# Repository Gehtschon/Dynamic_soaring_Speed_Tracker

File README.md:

# Dynamic_soaring_Speed_Tracker

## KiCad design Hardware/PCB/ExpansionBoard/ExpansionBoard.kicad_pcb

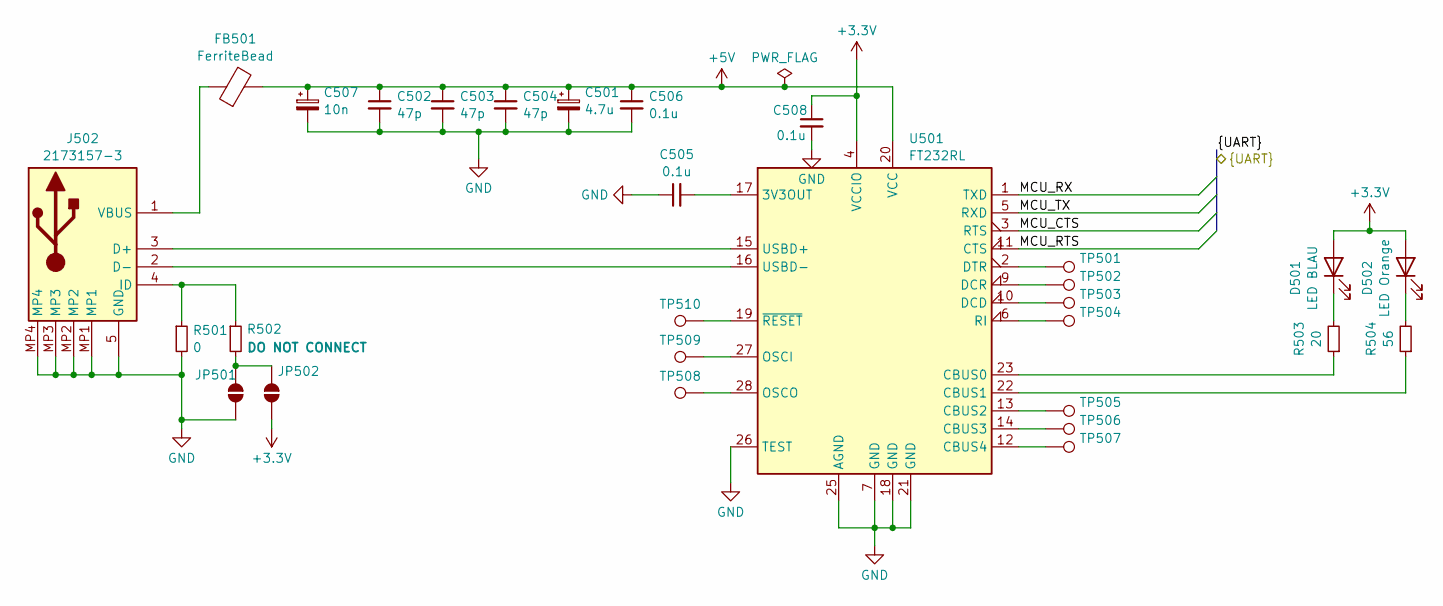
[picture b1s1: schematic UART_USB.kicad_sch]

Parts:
C501: 4.7u; C_0805_2012Metric_Pad1.18x1.45mm_HandSolder
C502, C503, C504: 47p; C_0805_2012Metric_Pad1.18x1.45mm_HandSolder
C505, C506, C508: 0.1u; C_0805_2012Metric_Pad1.18x1.45mm_HandSolder
C507: 10n; C_0805_2012Metric_Pad1.18x1.45mm_HandSolder
D501: LED BLAU; LEDM2012X100N
D502: LED Orange; R_0805_2012Metric
FB501: FerriteBead; C_0805_2012Metric_Pad1.18x1.45mm_HandSolder
J502: 2173157-3; 21731573; Mouser Part Number 571-2173157-3
JP501, JP502: SolderJumper_2_Open; SolderJumper-2_P1.3mm_Open_RoundedPad1.0x1.5mm
R501: 0; R_0805_2012Metric_Pad1.20x1.40mm_HandSolder
R502: DO NOT CONNECT; R_0805_2012Metric_Pad1.20x1.40mm_HandSolder
R503: 20; R_0805_2012Metric_Pad1.20x1.40mm_HandSolder
R504: 56; R_0805_2012Metric_Pad1.20x1.40mm_HandSolder
TP501, TP502, TP503, TP504, TP505, TP506, TP507, TP508, TP509, TP510: TestPoint; TestPoint_Pad_D1.5mm
U501: FT232RL; SSOP-28_5.3x10.2mm_P0.65mm

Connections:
+3.3V: C508.1, D501.2 (A), D502.2 (A), JP502.1 (A), U501.4 (VCCIO); also elsewhere on the board
+5V: C501.1, C502.1, C503.1, C504.1, C506.1, C507.1, FB501.2, U501.20 (VCC); also elsewhere on the board
/MCU Sheet/MCU_CTS: U501.3 (RTS); also elsewhere on the board
/MCU Sheet/MCU_RTS: U501.11 (CTS); also elsewhere on the board
/MCU Sheet/MCU_RX: U501.1 (TXD); also elsewhere on the board
/MCU Sheet/MCU_TX: U501.5 (RXD); also elsewhere on the board
GND: C501.2, C502.2, C503.2, C504.2, C505.1, C506.2, C507.2, C508.2, J502.5 (GND), J502.MP1, J502.MP2, J502.MP3, J502.MP4, JP501.1 (A), R501.2, U501.7 (GND), U501.18 (GND), U501.21 (GND), U501.25 (AGND), U501.26 (TEST); also elsewhere on the board
unnamed: D501.1 (K), R503.2
unnamed: D502.1 (K), R504.2
unnamed: J502.3 (D+), U501.15 (USBD+)
unnamed: J502.2 (D-), U501.16 (USBD-)
unnamed: J502.4 (ID), R501.1, R502.1
unnamed: FB501.1, J502.1 (VBUS)
unnamed: JP501.2 (B), JP502.2 (B), R502.2
unnamed: C505.2, U501.17 (3V3OUT)
unnamed: R503.1, U501.23 (CBUS0)
unnamed: R504.1, U501.22 (CBUS1)
unnamed: TP505.1, U501.13 (CBUS2)
unnamed: TP506.1, U501.14 (CBUS3)
unnamed: TP507.1, U501.12 (CBUS4)
unnamed: TP503.1, U501.10 (DCD)
unnamed: TP502.1, U501.9 (DCR)
unnamed: TP501.1, U501.2 (DTR)
unnamed: TP509.1, U501.27 (OSCI)
unnamed: TP508.1, U501.28 (OSCO)
unnamed: TP504.1, U501.6 (RI)
unnamed: TP510.1, U501.19 (~RESET)

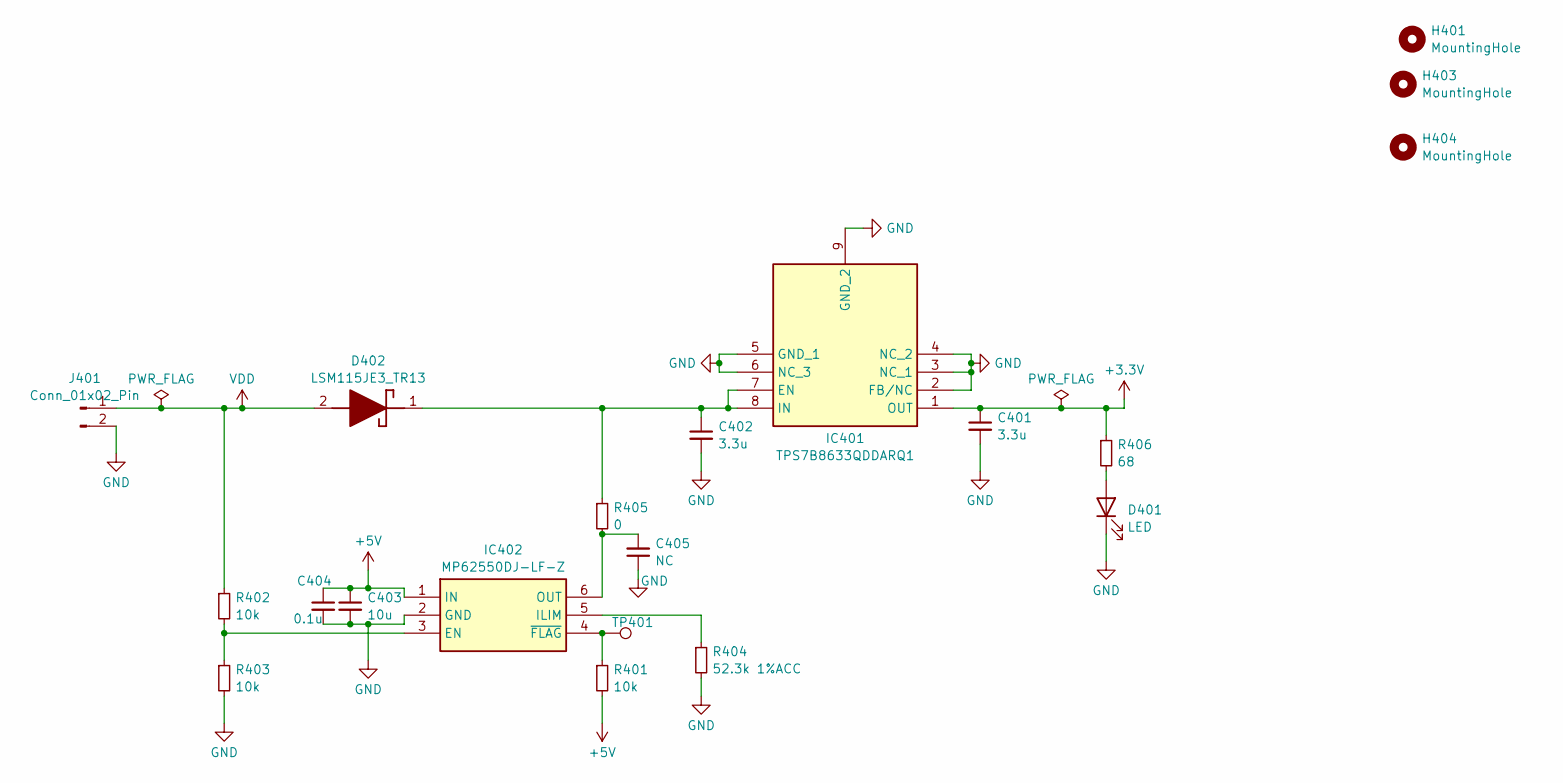
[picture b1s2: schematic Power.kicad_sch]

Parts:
C401, C402: 3.3u; C_0805_2012Metric_Pad1.18x1.45mm_HandSolder
C403: 10u; C_0805_2012Metric_Pad1.18x1.45mm_HandSolder
C404: 0.1u; C_0805_2012Metric_Pad1.18x1.45mm_HandSolder
C405: NC; C_0805_2012Metric_Pad1.18x1.45mm_HandSolder
D401: LED; LEDC2012X80N
D402: LSM115JE3_TR13; DIOM5436X330N; Mouser Part Number 494-LSM115JE3/TR13
H401, H403, H404: MountingHole; MountingHole_2.2mm_M2
IC401: TPS7B8633QDDARQ1; SOIC127P600X170-9N; Mouser Part Number 595-TPS7B8633QDDARQ1
IC402: MP62550DJ-LF-Z; SOT95P280X100-6N; Mouser Part Number 946-MP62550DJLFZ
J401: Conn_01x02_Pin; PinHeader_1x02_P2.54mm_Vertical
R401, R402, R403: 10k; R_0805_2012Metric_Pad1.20x1.40mm_HandSolder
R404: 52.3k 1%ACC; R_0805_2012Metric_Pad1.20x1.40mm_HandSolder
R405: 0; R_0805_2012Metric_Pad1.20x1.40mm_HandSolder
R406: 68; R_0805_2012Metric_Pad1.20x1.40mm_HandSolder
TP401: TestPoint; TestPoint_Pad_D1.5mm

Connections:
+3.3V: C401.1, IC401.1 (OUT), R406.1; also elsewhere on the board
+5V: C403.1, C404.1, IC402.1 (IN), R401.2; also elsewhere on the board
GND: C401.2, C402.2, C403.2, C404.2, C405.1, D401.1 (K), IC401.2 (FB/NC), IC401.3 (NC_1), IC401.4 (NC_2), IC401.5 (GND_1), IC401.6 (NC_3), IC401.9 (GND_2), IC402.2 (GND), J401.2, R403.2, R404.2; also elsewhere on the board
unnamed: D401.2 (A), R406.2
unnamed: C402.1, D402.1 (K), IC401.7 (EN), IC401.8 (IN), R405.1
unnamed: IC402.3 (EN), R402.2, R403.1
unnamed: IC402.5 (ILIM), R404.1
unnamed: C405.2, IC402.6 (OUT), R405.2
unnamed: IC402.4 (~FLAG), R401.1, TP401.1
VDD: D402.2 (A), J401.1, R402.1

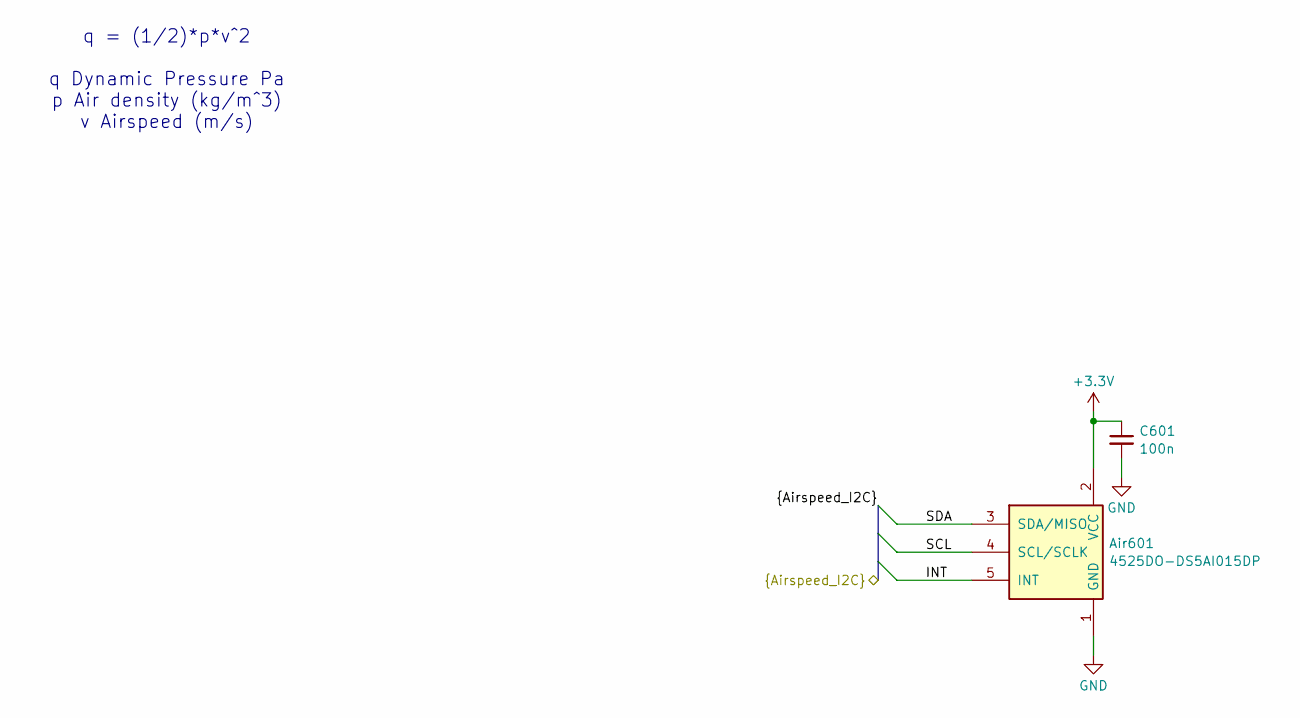
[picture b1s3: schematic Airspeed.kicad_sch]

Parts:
Air601: 4525DO-DS5AI015DP
C601: 100n; C_0805_2012Metric_Pad1.18x1.45mm_HandSolder

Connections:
+3.3V: Air601.2 (VCC), C601.1; also elsewhere on the board
/Airspeed Sheet/INT: Air601.5 (INT); also elsewhere on the board
/Airspeed Sheet/SCL: Air601.4 (SCL/SCLK); also elsewhere on the board
/Airspeed Sheet/SDA: Air601.3 (SDA/MISO); also elsewhere on the board
GND: Air601.1 (GND), C601.2; also elsewhere on the board

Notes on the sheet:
q = (1/2)*p*v^2 q Dynamic Pressure Pa p Air density (kg/m^3) v Airspeed (m/s)

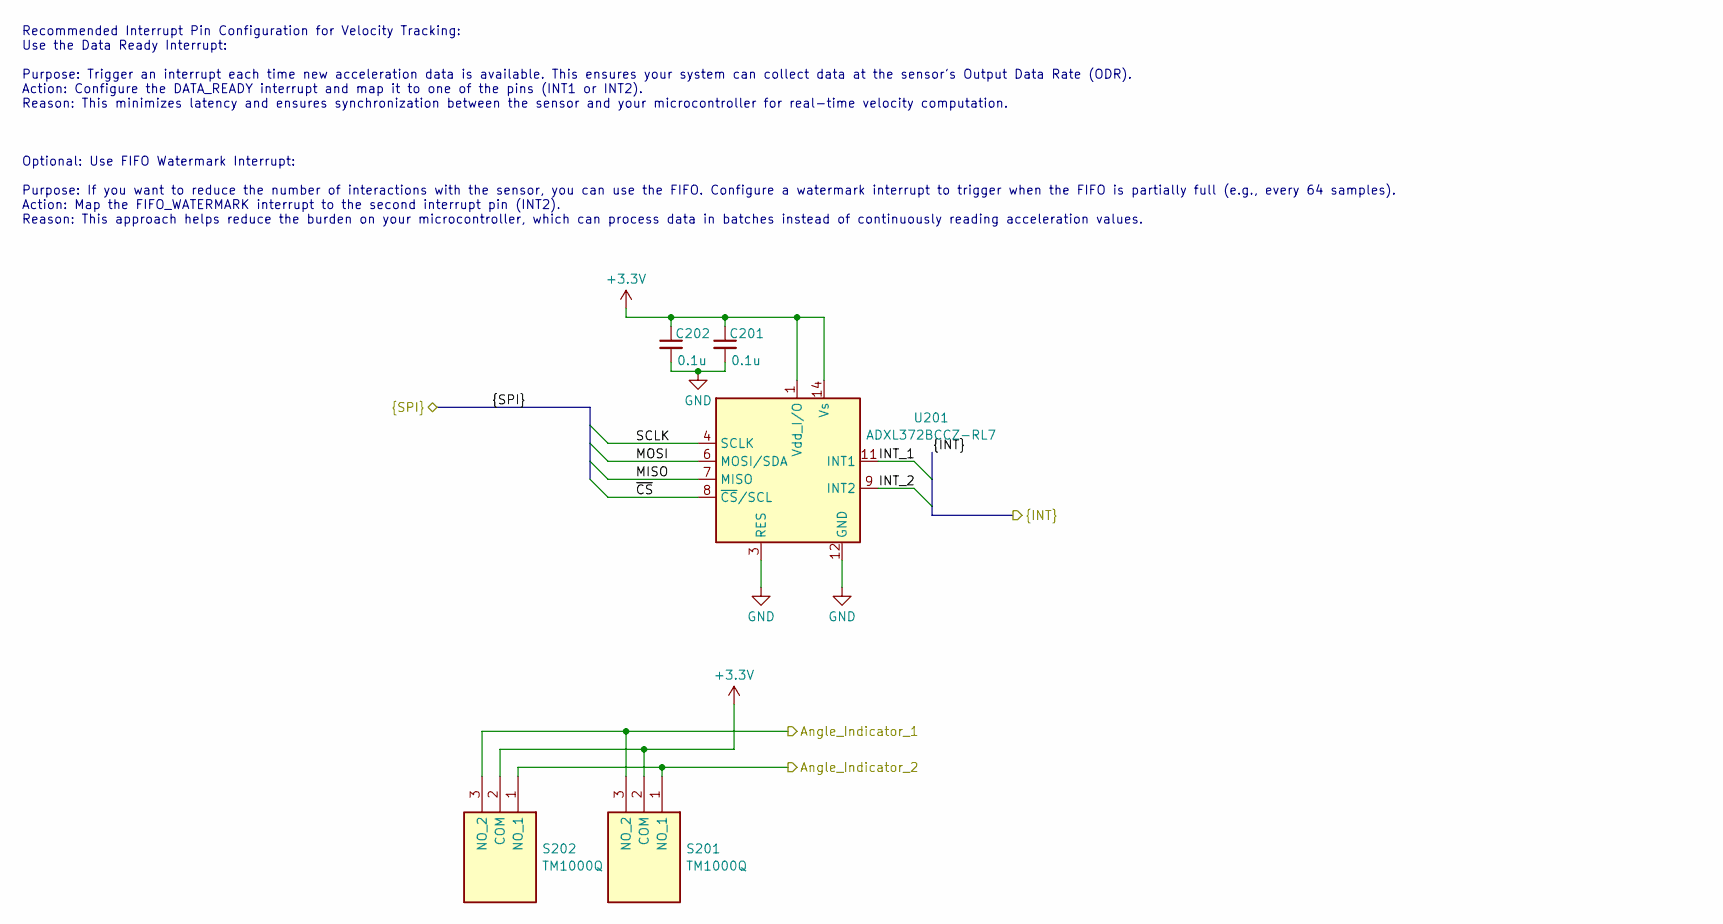
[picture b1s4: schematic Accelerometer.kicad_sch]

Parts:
C201, C202: 0.1u; C_0805_2012Metric_Pad1.18x1.45mm_HandSolder
S201, S202: TM1000Q; Mouser Part Number 612-TM1000Q
U201: ADXL372BCCZ-RL7

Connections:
+3.3V: C201.1, C202.1, S201.2 (COM), S202.2 (COM), U201.1 (Vdd_I/O), U201.14 (Vs); also elsewhere on the board
/Accelerometer.Sheet/Angle_Indicator_1: S201.3 (NO_2), S202.3 (NO_2); also elsewhere on the board
/Accelerometer.Sheet/Angle_Indicator_2: S201.1 (NO_1), S202.1 (NO_1); also elsewhere on the board
/Accelerometer.Sheet/INT_1: U201.11 (INT1); also elsewhere on the board
/Accelerometer.Sheet/INT_2: U201.9 (INT2); also elsewhere on the board
/Accelerometer.Sheet/MISO: U201.7 (MISO); also elsewhere on the board
/Accelerometer.Sheet/MOSI: U201.6 (MOSI/SDA); also elsewhere on the board
/Accelerometer.Sheet/SCLK: U201.4 (SCLK); also elsewhere on the board
/Accelerometer.Sheet/~CS: U201.8 (~CS/SCL); also elsewhere on the board
GND: C201.2, C202.2, U201.3 (RES), U201.5 (RES), U201.10 (RES), U201.12 (GND), U201.13 (GND), U201.16 (GND); also elsewhere on the board

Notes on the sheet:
Recommended Interrupt Pin Configuration for Velocity Tracking: Use the Data Ready Interrupt: Purpose: Trigger an interrupt each time new acceleration data is available. This ensures your system can collect data at the sensor's Output Data Rate (ODR). Action: Configure the DATA_READY interrupt and m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

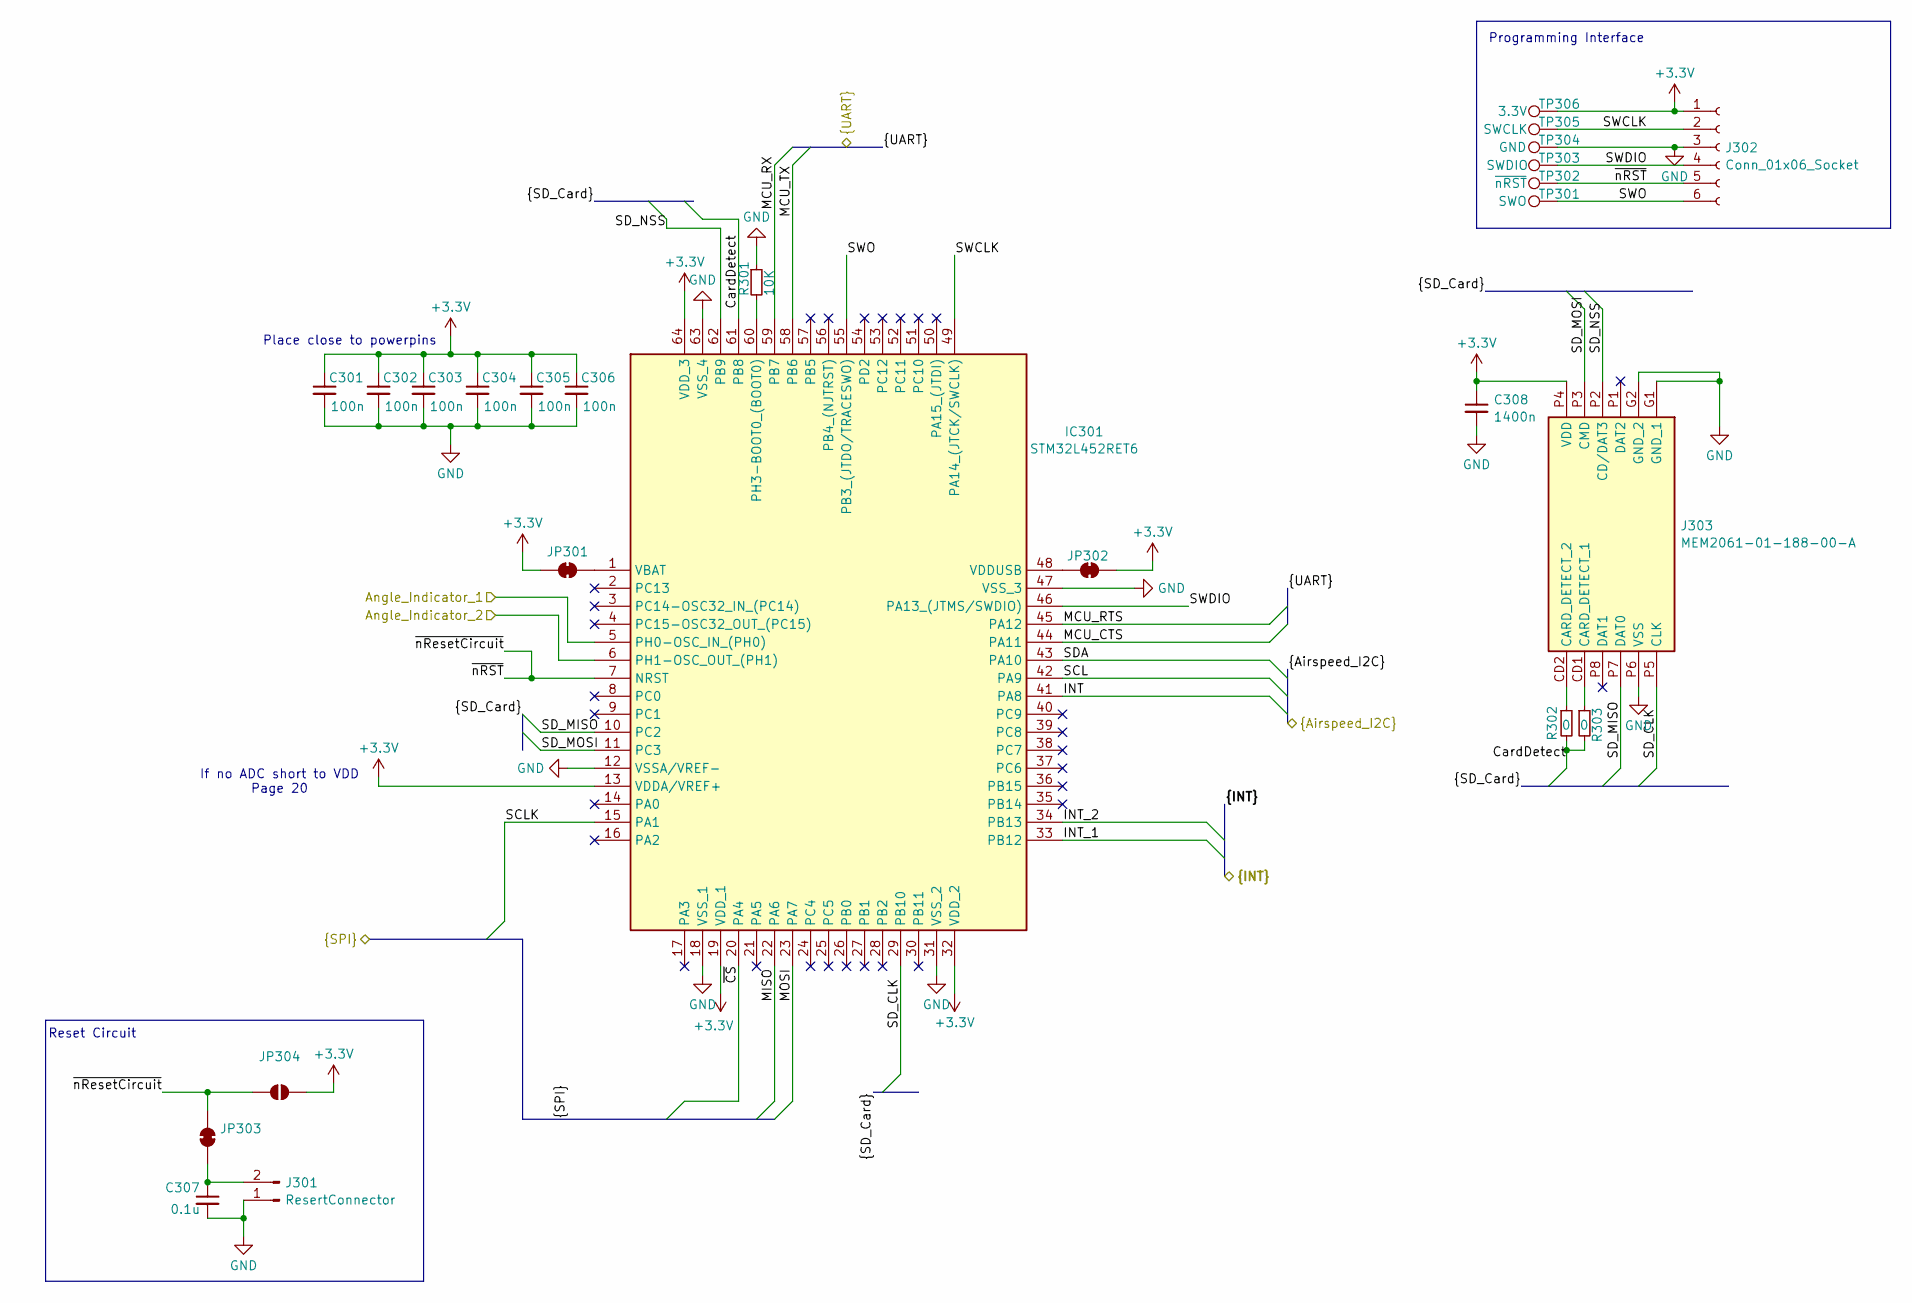
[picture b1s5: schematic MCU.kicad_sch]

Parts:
C301, C302, C303, C304, C305, C306: 100n; C_0805_2012Metric_Pad1.18x1.45mm_HandSolder
C307: 0.1u; C_0805_2012Metric_Pad1.18x1.45mm_HandSolder
C308: 1400n; C_0805_2012Metric_Pad1.18x1.45mm_HandSolder
IC301: STM32L452RET6; QFP50P1200X1200X160-64N; Mouser Part Number 511-STM32L452RET6
J301: ResertConnector; PinHeader_1x02_P2.54mm_Vertical
J302: Conn_01x06_Socket; Tag-Connect_TC2030-IDC-FP_2x03_P1.27mm_Vertical
J303: MEM2061-01-188-00-A; MEM20610118800A; Mouser Part Number 640-MEM20610118800A
JP301, JP302, JP303: SolderJumper_2_Bridged; SolderJumper-2_P1.3mm_Bridged_RoundedPad1.0x1.5mm
JP304: SolderJumper_2_Open; SolderJumper-2_P1.3mm_Open_RoundedPad1.0x1.5mm
R301: 10K; R_0805_2012Metric_Pad1.20x1.40mm_HandSolder
R302, R303: 0; R_0805_2012Metric_Pad1.20x1.40mm_HandSolder
TP301: SWO; TestPoint_Pad_D1.5mm
TP302: ~{nRST}; TestPoint_Pad_D1.5mm
TP303: SWDIO; TestPoint_Pad_D1.5mm
TP304: GND; TestPoint_Pad_D1.5mm
TP305: SWCLK; TestPoint_Pad_D1.5mm
TP306: 3.3V; TestPoint_Pad_D1.5mm

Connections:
+3.3V: C301.1, C302.1, C303.1, C304.1, C305.1, C306.1, C308.1, IC301.13 (VDDA/VREF+), IC301.19 (VDD_1), IC301.32 (VDD_2), IC301.64 (VDD_3), J302.1, J303.P4 (VDD), JP301.1 (A), JP302.1 (A), JP304.2 (B), TP306.1; also elsewhere on the board
/Accelerometer.Sheet/Angle_Indicator_1: IC301.5 (PH0-OSC_IN_(PH0)); also elsewhere on the board
/Accelerometer.Sheet/Angle_Indicator_2: IC301.6 (PH1-OSC_OUT_(PH1)); also elsewhere on the board
/Accelerometer.Sheet/INT_1: IC301.33 (PB12); also elsewhere on the board
/Accelerometer.Sheet/INT_2: IC301.34 (PB13); also elsewhere on the board
/Accelerometer.Sheet/MISO: IC301.22 (PA6); also elsewhere on the board
/Accelerometer.Sheet/MOSI: IC301.23 (PA7); also elsewhere on the board
/Accelerometer.Sheet/SCLK: IC301.15 (PA1); also elsewhere on the board
/Accelerometer.Sheet/~CS: IC301.20 (PA4); also elsewhere on the board
/Airspeed Sheet/INT: IC301.41 (PA8); also elsewhere on the board
/Airspeed Sheet/SCL: IC301.42 (PA9); also elsewhere on the board
/Airspeed Sheet/SDA: IC301.43 (PA10); also elsewhere on the board
/MCU Sheet/CardDetect: IC301.61 (PB8), R302.2, R303.2
/MCU Sheet/MCU_CTS: IC301.44 (PA11); also elsewhere on the board
/MCU Sheet/MCU_RTS: IC301.45 (PA12); also elsewhere on the board
/MCU Sheet/MCU_RX: IC301.59 (PB7); also elsewhere on the board
/MCU Sheet/MCU_TX: IC301.58 (PB6); also elsewhere on the board
/MCU Sheet/SD_CLK: IC301.29 (PB10), J303.P5 (CLK)
/MCU Sheet/SD_MISO: IC301.10 (PC2), J303.P7 (DAT0)
/MCU Sheet/SD_MOSI: IC301.11 (PC3), J303.P3 (CMD)
/MCU Sheet/SD_NSS: IC301.62 (PB9), J303.P2 (CD/DAT3)
/MCU Sheet/SWCLK: IC301.49 (PA14_(JTCK/SWCLK)), J302.2, TP305.1
/MCU Sheet/SWDIO: IC301.46 (PA13_(JTMS/SWDIO)), J302.4, TP303.1
/MCU Sheet/SWO: IC301.55 (PB3_(JTDO/TRACESWO)), J302.6, TP301.1
/MCU Sheet/~nRST: IC301.7 (NRST), J302.5, JP303.2 (B), JP304.1 (A), TP302.1
GND: C301.2, C302.2, C303.2, C304.2, C305.2, C306.2, C307.2, C308.2, IC301.12 (VSSA/VREF-), IC301.18 (VSS_1), IC301.31 (VSS_2), IC301.47 (VSS_3), IC301.63 (VSS_4), J301.1, J302.3, J303.G1 (GND_1), J303.G2 (GND_2), J303.P6 (VSS), R301.1, TP304.1; also elsewhere on the board
unnamed: IC301.60 (PH3-BOOT0_(BOOT0)), R301.2
unnamed: IC301.1 (VBAT), JP301.2 (B)
unnamed: IC301.48 (VDDUSB), JP302.2 (B)
unnamed: C307.1, J301.2, JP303.1 (A)
unnamed: J303.CD1 (CARD_DETECT_1), R303.1
unnamed: J303.CD2 (CARD_DETECT_2), R302.1

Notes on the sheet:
Programming Interface
If no ADC short to VDD Page 20
Reset Circuit
Place close to powerpins

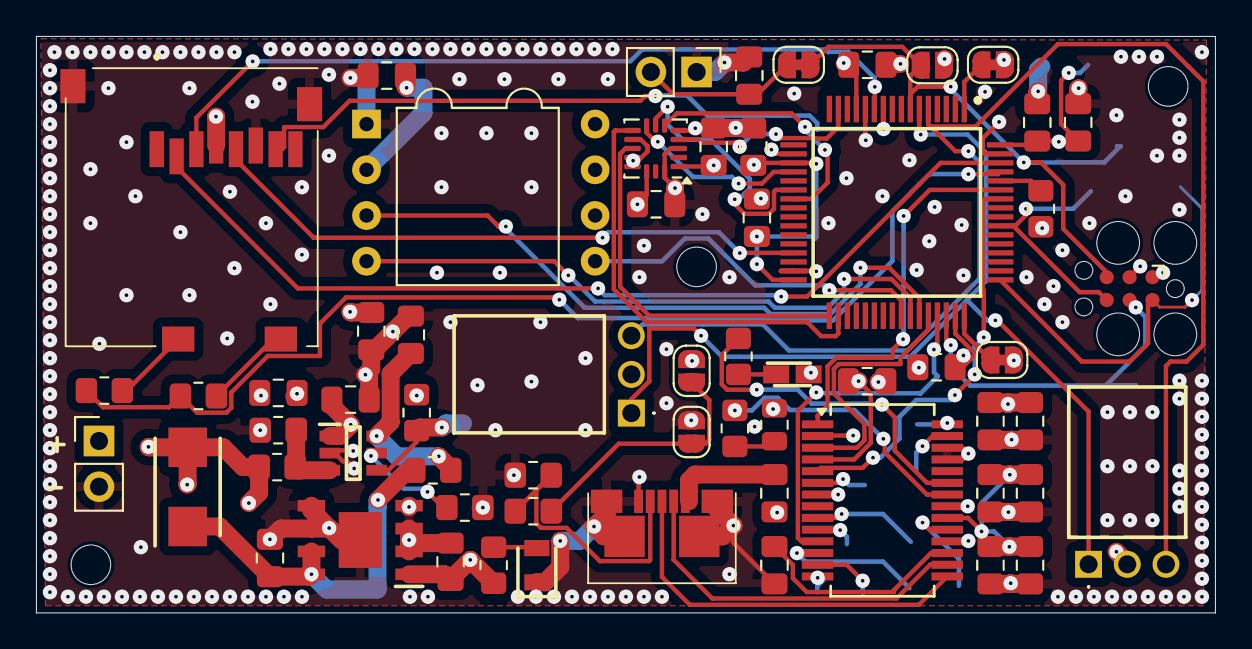
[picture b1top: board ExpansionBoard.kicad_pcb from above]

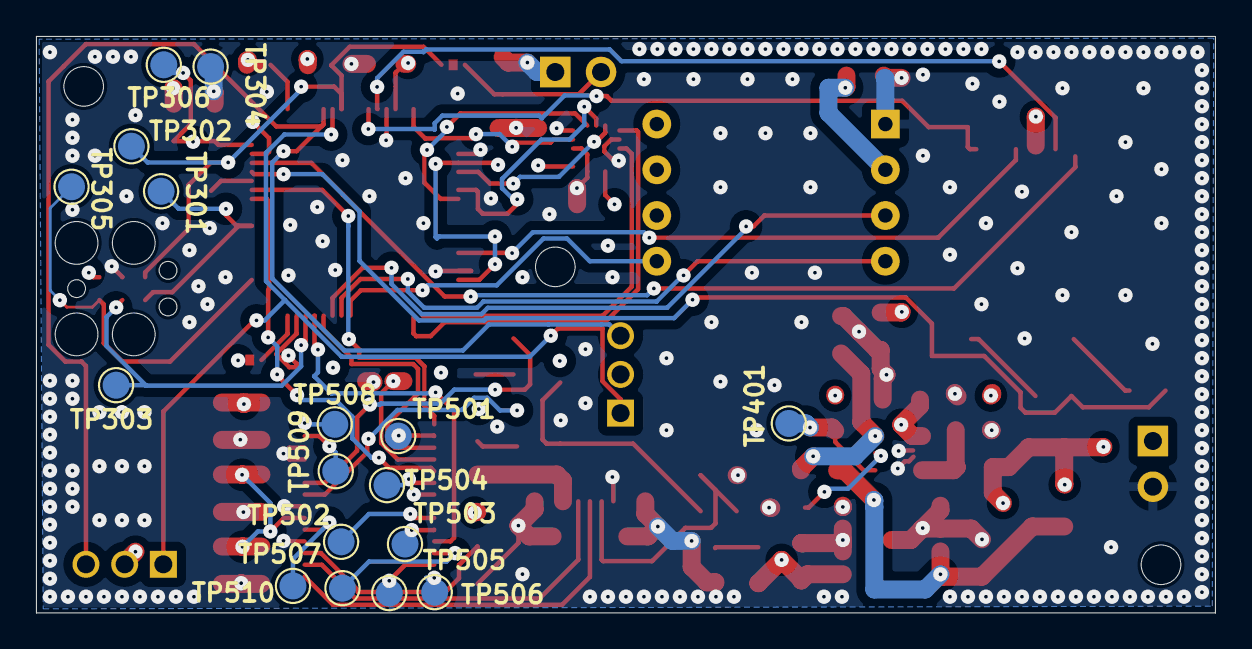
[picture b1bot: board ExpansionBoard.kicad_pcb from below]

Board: 4 copper layers, 65.5 x 32.0 mm, 81 parts (17 on the bottom side), 60 nets.

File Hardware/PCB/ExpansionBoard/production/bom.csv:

Designator,Footprint,Quantity,Value,LCSC Part #
AIR601,4525DO-DS5AI015DP,1,4525DO-DS5AI015DP,
"C201, C202, C307, C404, C505, C506, C508",0805,7,0.1u,
"C301, C302, C303, C304, C305, C306, C601",0805,7,100n,
C308,0805,1,1400n,
"C401, C402",0805,2,3.3u,
C403,0805,1,10u,
C405,0805,1,NC,
C501,0805,1,4.7u,
"C502, C503, C504",0805,3,47p,
C507,0805,1,10n,
D401,LEDC2012X80N,1,LED,
D402,DIOM5436X330N,1,LSM115JE3_TR13,
D501,LEDM2012X100N,1,LED BLAU,
D502,0805,1,LED Orange,
FB501,0805,1,FerriteBead,
IC301,QFP50P1200X1200X160-64N,1,STM32L452RET6,
IC401,SOIC127P600X170-9N,1,TPS7B8633QDDARQ1,
IC402,SOT95P280X100-6N,1,MP62550DJ-LF-Z,
J301,PinHeader_1x02_P2.54mm_Vertical,1,ResertConnector,
J302,Tag-Connect_TC2030-IDC-FP_2x03_P1.27mm_Vertical,1,Conn_01x06_Socket,
J303,MEM20610118800A,1,MEM2061-01-188-00-A,
J401,PinHeader_1x02_P2.54mm_Vertical,1,Conn_01x02_Pin,
J502,21731573,1,2173157-3,
"R301, R401, R402, R403",0805,4,10K,
"R302, R303, R405, R501",0805,4,0,
R404,0805,1,52.3k 1%ACC,
R406,0805,1,68,
R502,0805,1,DO NOT CONNECT,
R503,0805,1,20,
R504,0805,1,56,
"S201, S202",TM1000Q,2,TM1000Q,
TP301,TestPoint_Pad_D1.5mm,1,SWO,
TP302,TestPoint_Pad_D1.5mm,1,~{nRST},
TP303,TestPoint_Pad_D1.5mm,1,SWDIO,
TP304,TestPoint_Pad_D1.5mm,1,GND,
TP305,TestPoint_Pad_D1.5mm,1,SWCLK,
TP306,TestPoint_Pad_D1.5mm,1,3.3V,
"TP401, TP501, TP502, TP503, TP504, TP505, TP506, TP507, TP508, TP509, TP510",TestPoint_Pad_D1.5mm,11,TestPoint,
U201,ADXL372BCCZ-RL7,1,ADXL372BCCZ-RL7,
U501,SSOP-28_5.3x10.2mm_P0.65mm,1,FT232RL,

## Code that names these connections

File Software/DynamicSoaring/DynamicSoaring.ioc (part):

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Mcu.Name=STM32L452R(C-E)Tx
Mcu.Package=LQFP64
Mcu.UserName=STM32L452RETx
PA1.Mode=Full_Duplex_Master
PA1.Signal=SPI1_SCK
PA10.Mode=I2C
PA10.Signal=I2C1_SDA
PA11.Mode=CTS_RTS
PA11.Signal=USART1_CTS
PA12.Mode=CTS_RTS
PA12.Signal=USART1_RTS
PA4.Mode=NSS_Signal_Hard_Output
PA4.Signal=SPI1_NSS
PA6.Mode=Full_Duplex_Master
PA6.Signal=SPI1_MISO
PA7.Mode=Full_Duplex_Master
PA7.Signal=SPI1_MOSI
PA8.Signal=GPXTI8
PA9.Mode=I2C
PA9.Signal=I2C1_SCL
PB10.Mode=Full_Duplex_Master
PB10.Signal=SPI2_SCK
PB12.GPIOParameters=GPIO_Label
PB12.GPIO_Label=ACC_INT_1
PB12.Signal=GPXTI12
PB13.GPIOParameters=GPIO_Label
PB13.GPIO_Label=ACC_INT_2
PB13.Signal=GPXTI13
PB6.Mode=Asynchronous
PB6.Signal=USART1_TX
PB7.Mode=Asynchronous
PB7.Signal=USART1_RX
PB8.GPIOParameters=GPIO_Label
PB8.GPIO_Label=SD_CD
PB8.Signal=GPIO_Output
PB9.Mode=NSS_Signal_Hard_Output
PB9.Signal=SPI2_NSS
PC2.Mode=Full_Duplex_Master
PC2.Signal=SPI2_MISO
PC3.Mode=Full_Duplex_Master
PC3.Signal=SPI2_MOSI
PH0-OSC_IN\ (PH0).Signal=GPXTI0
PH1-OSC_OUT\ (PH1).Signal=GPXTI1
RCC.HSE_VALUE=8000000
board=custom

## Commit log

2024-11-27 not to bad simulation :-)
2024-11-28 added noise calculation from datasheet
2024-12-01 added gitignore
2024-12-01 ACC Sheet almost finshied added SPI BUS
2024-12-02 INT BUS
2024-12-03 added POWER Sheet
2024-12-06 added PINOUT to mcu and UART USB CHIP
2024-12-07 added USB and Powerseitcher
2024-12-08 DONE: PWR LED MISSING AND AIRSPEED
2024-12-11 added Airspeed simulation and Footprint with 3D model
2024-12-13 Finished Airspeed Fotprint and symbol
2024-12-15 finished schema
2024-12-15 to pcb
2024-12-16 added Cube Project, SD Card and Tillt Switch
2024-12-19 finished pcb layout
2024-12-20 finsihed filling
2024-12-20 finsihed pcb
2025-01-01 Silkcreen color
2025-01-01 removed error in drc
2025-01-15 added boomm
